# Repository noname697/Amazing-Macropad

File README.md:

# ⌨️ Custom Manenti Macropad

This project consists of the complete development of a custom macropad keyboard, integrating the electronic circuit in **KiCad** and the case modeling in **Autodesk Fusion**.

## 📸 Project Demo

### Render / Screenshot of the Macropad Design

### Technical Drawing and 3D Modeling of the Case

---

## ⚡ Electronic Development (KiCad)

The circuit was designed to be compact and functional, using a microcontroller on one side of the board and the three switches on the other. The design has mounting holes strategically positioned in the four corners of the board.

### Electrical Schematic

### PCB Layout (Edge Cuts and Traces)

---

## 🛠️ Case Specifications (Fusion 360)

I modeled the panel case from scratch in Fusion using the .STEP file exported from KiCad as a base to get the correct measurements; I made something simple, but functional.

- **Internal PCB tolerance:** `0.4 mm` on each side to ensure clearance during assembly.
- **Wall thickness:** `13.0 mm` for high structural and acoustic resistance.
- **Base thickness:** `3.0 mm`.
- **cut to USB:** Aligned with the physical connector.
- **Mounting:** 4 reinforcing columns at the corners of the plate (taking care not to touch any "wires") with **Ø 4.7 mm** holes for screw installation.

---

## 📦 Bill of Materials

The table below lists all components required for the complete assembly of the structure:

| Item | Component                   | Quantity | Description / Specification                                |
| :--- | :-------------------------- | :------: | :--------------------------------------------------------- |
| 1    | Custom PCB                  |    1     | Printed circuit board developed in KiCad                   |
| 2    | XIAO_RP2040 microcontroller |    1     | Seeed Studio XIAO RP2040 or CircuitPython-compatible board |
| 3    | Mechanical switches         |    3     | Cherry MX-style switches or compatible                     |
| 4    | Keycaps                     |    3     | Keycaps compatible with MX switches                        |
| 5    | LEDs                        |    3     | LEDs connected to pin D3                                   |
| 6    | Heat-set inserts            |    4     | M3 × 5 × 4 mm brass inserts                                |
| 7    | M3 screws                   |    4     | M3 × 16 mm screws                                          |
| 8    | Bottom case                 |    1     | 3D-printed part based on the `Bottom.STEP` file            |
| 9    | Top cover / switch plate    |    1     | 3D-printed part based on the `Top.STEP` file               |
| 10   | USB-C cable                 |    1     | Cable for connecting the macropad to the computer          |

---# ⌨️ Custom Tecladinho Macropad

The macropad was designed to execute quick music commands:

- Key 1: previous track
- Key 2: next track
- Key 3: pause/play

---

## ⚡ Electronic Development

The project uses a CircuitPython-compatible microcontroller and three mechanical keys for media control.

### Used pins

| Function               | Pin |
| Key 1 — previous track | D0  |
| Key 2 — next track     | D1  |
| Key 3 — play/pause     | D2  |
| LEDs                   | D3  |

The three keys are used as digital inputs in the firmware, while the LEDs are controlled by pin D3.

---

## 💻 Firmware

The firmware was developed using **KMK**, which runs on top of **CircuitPython**. This choice makes keyboard configuration easier, allowing the key behavior to be edited directly in Python.

### Main file

The main firmware must be saved on the XIAO as:

```text
main.py
```

---

## 🚀 Exporting Files for Production

The mechanical files must be exported in **.STEP** format, not STL, to preserve the CAD geometry.

### Required files

```text
Top.STEP
Bottom.STEP
```

### Exporting in Fusion 360

1. In Fusion 360, make only the part you want to export visible.
2. Hide the PCB and the other components.
3. Right-click the desired component.
4. Select **Export**.
5. Choose the **STEP** format.
6. Export each part separately:

---

## 🧠 Author

Project developed by **Arthur Lima Manenti** as a custom 3-key macropad for media control.

---

I declared the use of AI in this Readme.md to form the basis of the document, but I checked and edited everything that was inconsistent and repetitive.

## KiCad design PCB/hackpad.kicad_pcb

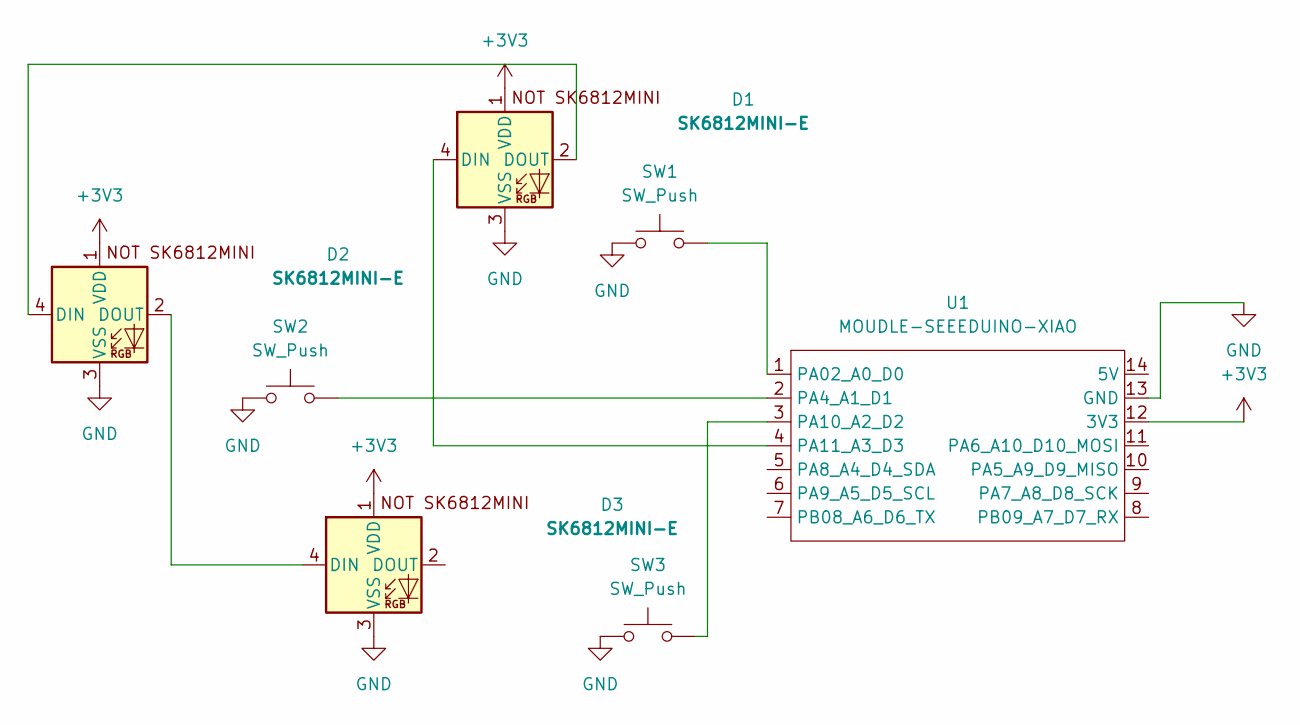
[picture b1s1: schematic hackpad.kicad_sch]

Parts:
D1, D2, D3: SK6812MINI-E; SK6812MINI-E_fixed
SW1, SW2, SW3: SW_Push; SW_Cherry_MX_1.00u_PCB
U1: MOUDLE-SEEEDUINO-XIAO; XIAO-Generic-Hybrid-14P-2.54-21X17.8MM

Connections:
+3V3: D1.1 (VDD), D2.1 (VDD), D3.1 (VDD), U1.12 (3V3)
GND: D1.3 (VSS), D2.3 (VSS), D3.3 (VSS), SW1.1, SW2.1, SW3.1, U1.13 (GND)
unnamed: D1.4 (DIN), U1.4 (PA11_A3_D3)
unnamed: D1.2 (DOUT), D2.4 (DIN)
unnamed: D2.2 (DOUT), D3.4 (DIN)
unnamed: SW1.2, U1.1 (PA02_A0_D0)
unnamed: SW2.2, U1.2 (PA4_A1_D1)
unnamed: SW3.2, U1.3 (PA10_A2_D2)

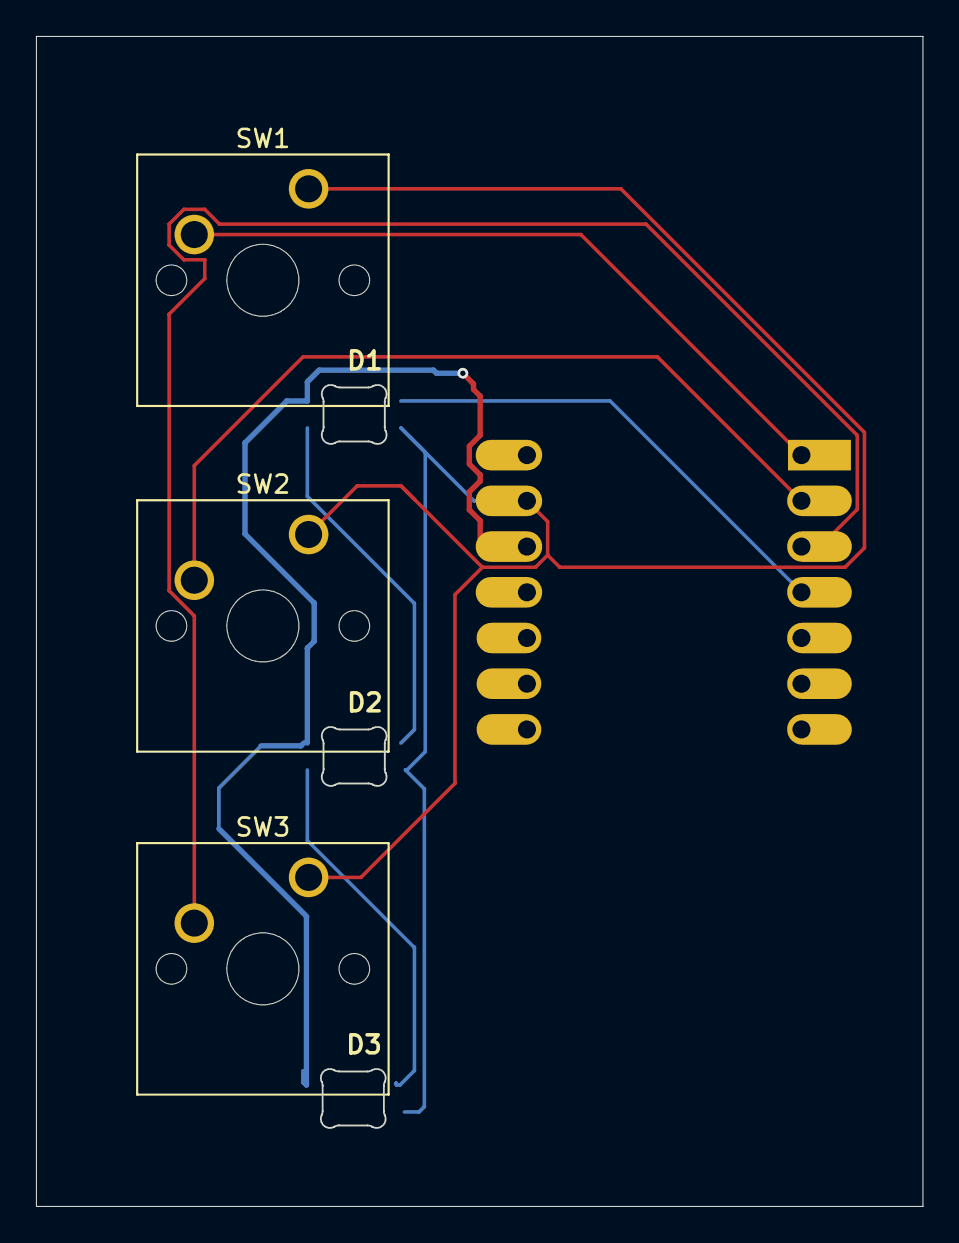
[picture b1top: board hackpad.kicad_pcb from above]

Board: 2 copper layers, 49.2 x 65.0 mm, 7 parts (1 on the bottom side), 8 nets.

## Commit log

2026-06-04 Translate Readme.md to english
2026-06-27 Adicionando BOM.csv
